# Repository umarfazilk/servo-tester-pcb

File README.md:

# Servo Tester PCB Design

A compact **Servo Motor Tester PCB** designed using **KiCad 10.0**.
This project is based on the **NE555 timer IC**, which generates a variable PWM signal to test and control standard servo motors.

The board includes a potentiometer for manual pulse width adjustment, input power connector, servo output connector, LED indicator, and a clean PCB layout with 3D visualization.

---

## Project Overview

This PCB is designed to test servo motors without using any microcontroller.
The NE555 timer is configured to generate a servo control signal, and the potentiometer allows the user to vary the output pulse width. This makes it useful for checking servo rotation, testing servo response, and basic electronics learning.

---

## Features

* NE555-based servo signal generation
* Potentiometer-controlled pulse adjustment
* Dedicated 3-pin servo output header
* Power input connector
* LED power/status indicator
* Compact PCB layout
* Through-hole component design for easy soldering
* KiCad schematic, PCB layout, and 3D model included

---

## Circuit Working

The circuit uses the **NE555 timer IC** in an astable/PWM signal generation configuration.
The timing components such as resistors, capacitor, diode, and potentiometer control the charge and discharge timing of the capacitor.

By rotating the potentiometer, the output pulse width changes.
This varying pulse signal is sent to the servo signal pin through the 3-pin output connector.

The servo connector provides:

* GND
* VCC
* SIG

The LED section is used as a power/status indication.

---

## Main Components Used

| Component          | Description                         |
| ------------------ | ----------------------------------- |
| NE555P             | Timer IC used for signal generation |
| 100K Potentiometer | Controls the servo pulse width      |
| 1N4148             | Signal diode for timing control     |
| 22nF Capacitor     | Timing capacitor                    |
| Resistors          | Timing and LED current limiting     |
| LED                | Power/status indicator              |
| 2-pin Header       | Power input                         |
| 3-pin Header       | Servo output connector              |

---

## PCB Preview

### 3D Model View 1

### 3D Model View 2

### PCB Layout

### Schematic

---

## Project Files

| File                     | Description                               |
| ------------------------ | ----------------------------------------- |
| `servo tester.kicad_pro` | KiCad project file                        |
| `servo tester.kicad_sch` | Schematic file                            |
| `servo tester.kicad_pcb` | PCB layout file                           |
| `3d model 1.png`         | 3D render image                           |
| `3d model 2.png`         | 3D render image                           |
| `layout img.png`         | PCB layout image                          |
| `schematic img.png`      | Circuit schematic image                   |
| `.gitignore`             | Git ignore file for KiCad temporary files |

---

## Applications

* Servo motor testing
* PWM signal generation learning
* 555 timer practical circuit study
* Basic PCB design practice
* Electronics mini project
* Hardware prototyping and testing

---

## Tools Used

* KiCad 10.0
* PCB Editor
* Schematic Editor
* 3D Viewer

---

## Learning Outcome

Through this project, I practiced:

* NE555 timer-based circuit design
* Servo motor control signal concept
* Schematic design in KiCad
* PCB layout routing
* Component placement
* 3D PCB visualization
* GitHub project documentation

---

## Author

**Umar Fazil K**
Electronics and Communication Engineering Student
Passionate about Electronics, PCB Design, Embedded Systems, and Hardware Development.

---

## License

This project is open for learning and educational purposes.

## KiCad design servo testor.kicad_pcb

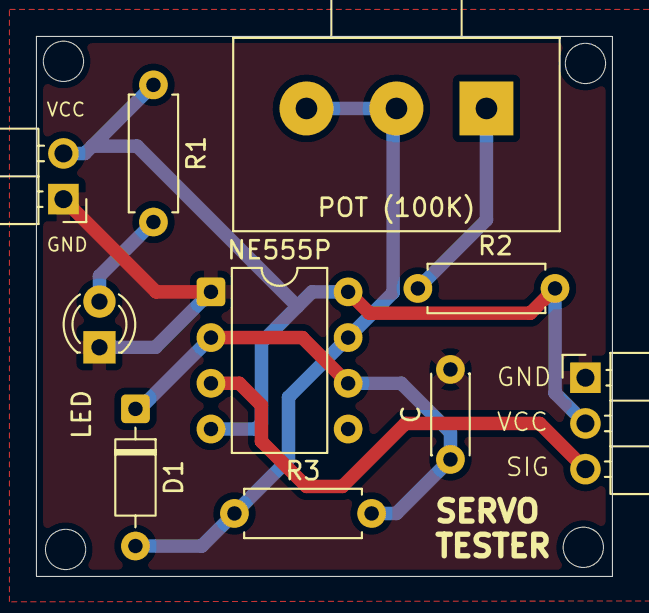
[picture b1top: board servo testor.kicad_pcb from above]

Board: 2 copper layers, 32.0 x 30.0 mm, 10 parts (0 on the bottom side), 7 nets.

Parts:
C: 22nF; C_Disc_D4.3mm_W1.9mm_P5.00mm
D1: 1N4148; D_DO-35_SOD27_P7.62mm_Horizontal
J1: Conn_01x02_Pin; PinHeader_1x02_P2.54mm_Horizontal
J2: Conn_01x03_Pin; PinHeader_1x03_P2.54mm_Horizontal
LED: LED; LED_D3.0mm
NE555P: NE555P; DIP-8_W7.62mm
POT (100K): 100K; Potentiometer_Alps_RK163_Single_Horizontal
R1: 1K; R_Axial_DIN0207_L6.3mm_D2.5mm_P7.62mm_Horizontal
R2: 56K; R_Axial_DIN0207_L6.3mm_D2.5mm_P7.62mm_Horizontal
R3: 3M3; R_Axial_DIN0207_L6.3mm_D2.5mm_P7.62mm_Horizontal

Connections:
/SIG: J2.3, NE555P.3 (OUT)
/VCC: J1.2, J2.2, NE555P.4 (~RST), NE555P.8 (VCC), R1.1, R2.2
GND: C.2, J1.1, J2.1, LED.1 (K), NE555P.1 (GND)
unnamed: D1.2 (A), NE555P.7 (DISCH), POT (100K).2, POT (100K).3, R3.1
unnamed: C.1, D1.1 (K), NE555P.2 (TRIG), NE555P.6 (THRES), R3.2
unnamed: LED.2 (A), R1.2
unnamed: POT (100K).1, R2.1

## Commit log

2026-06-22 Add servo tester PCB design
2026-06-22 BILL OF MATERIAL
